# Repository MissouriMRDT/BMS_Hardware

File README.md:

Battery Management System- this year it DOES THINGS (for real though!).

New for 2022: <br/>
-Designed to monitor an 8s8p LiPo battery pack at a max 33.6V @ 160A peak. <br/>
-The Cell Monitoring circuit uses the AS358MTR-E1 Op-Amp as it could be powered off of pack voltage. <br/>
-Teensy 4.1 used as microcontroller for the board.

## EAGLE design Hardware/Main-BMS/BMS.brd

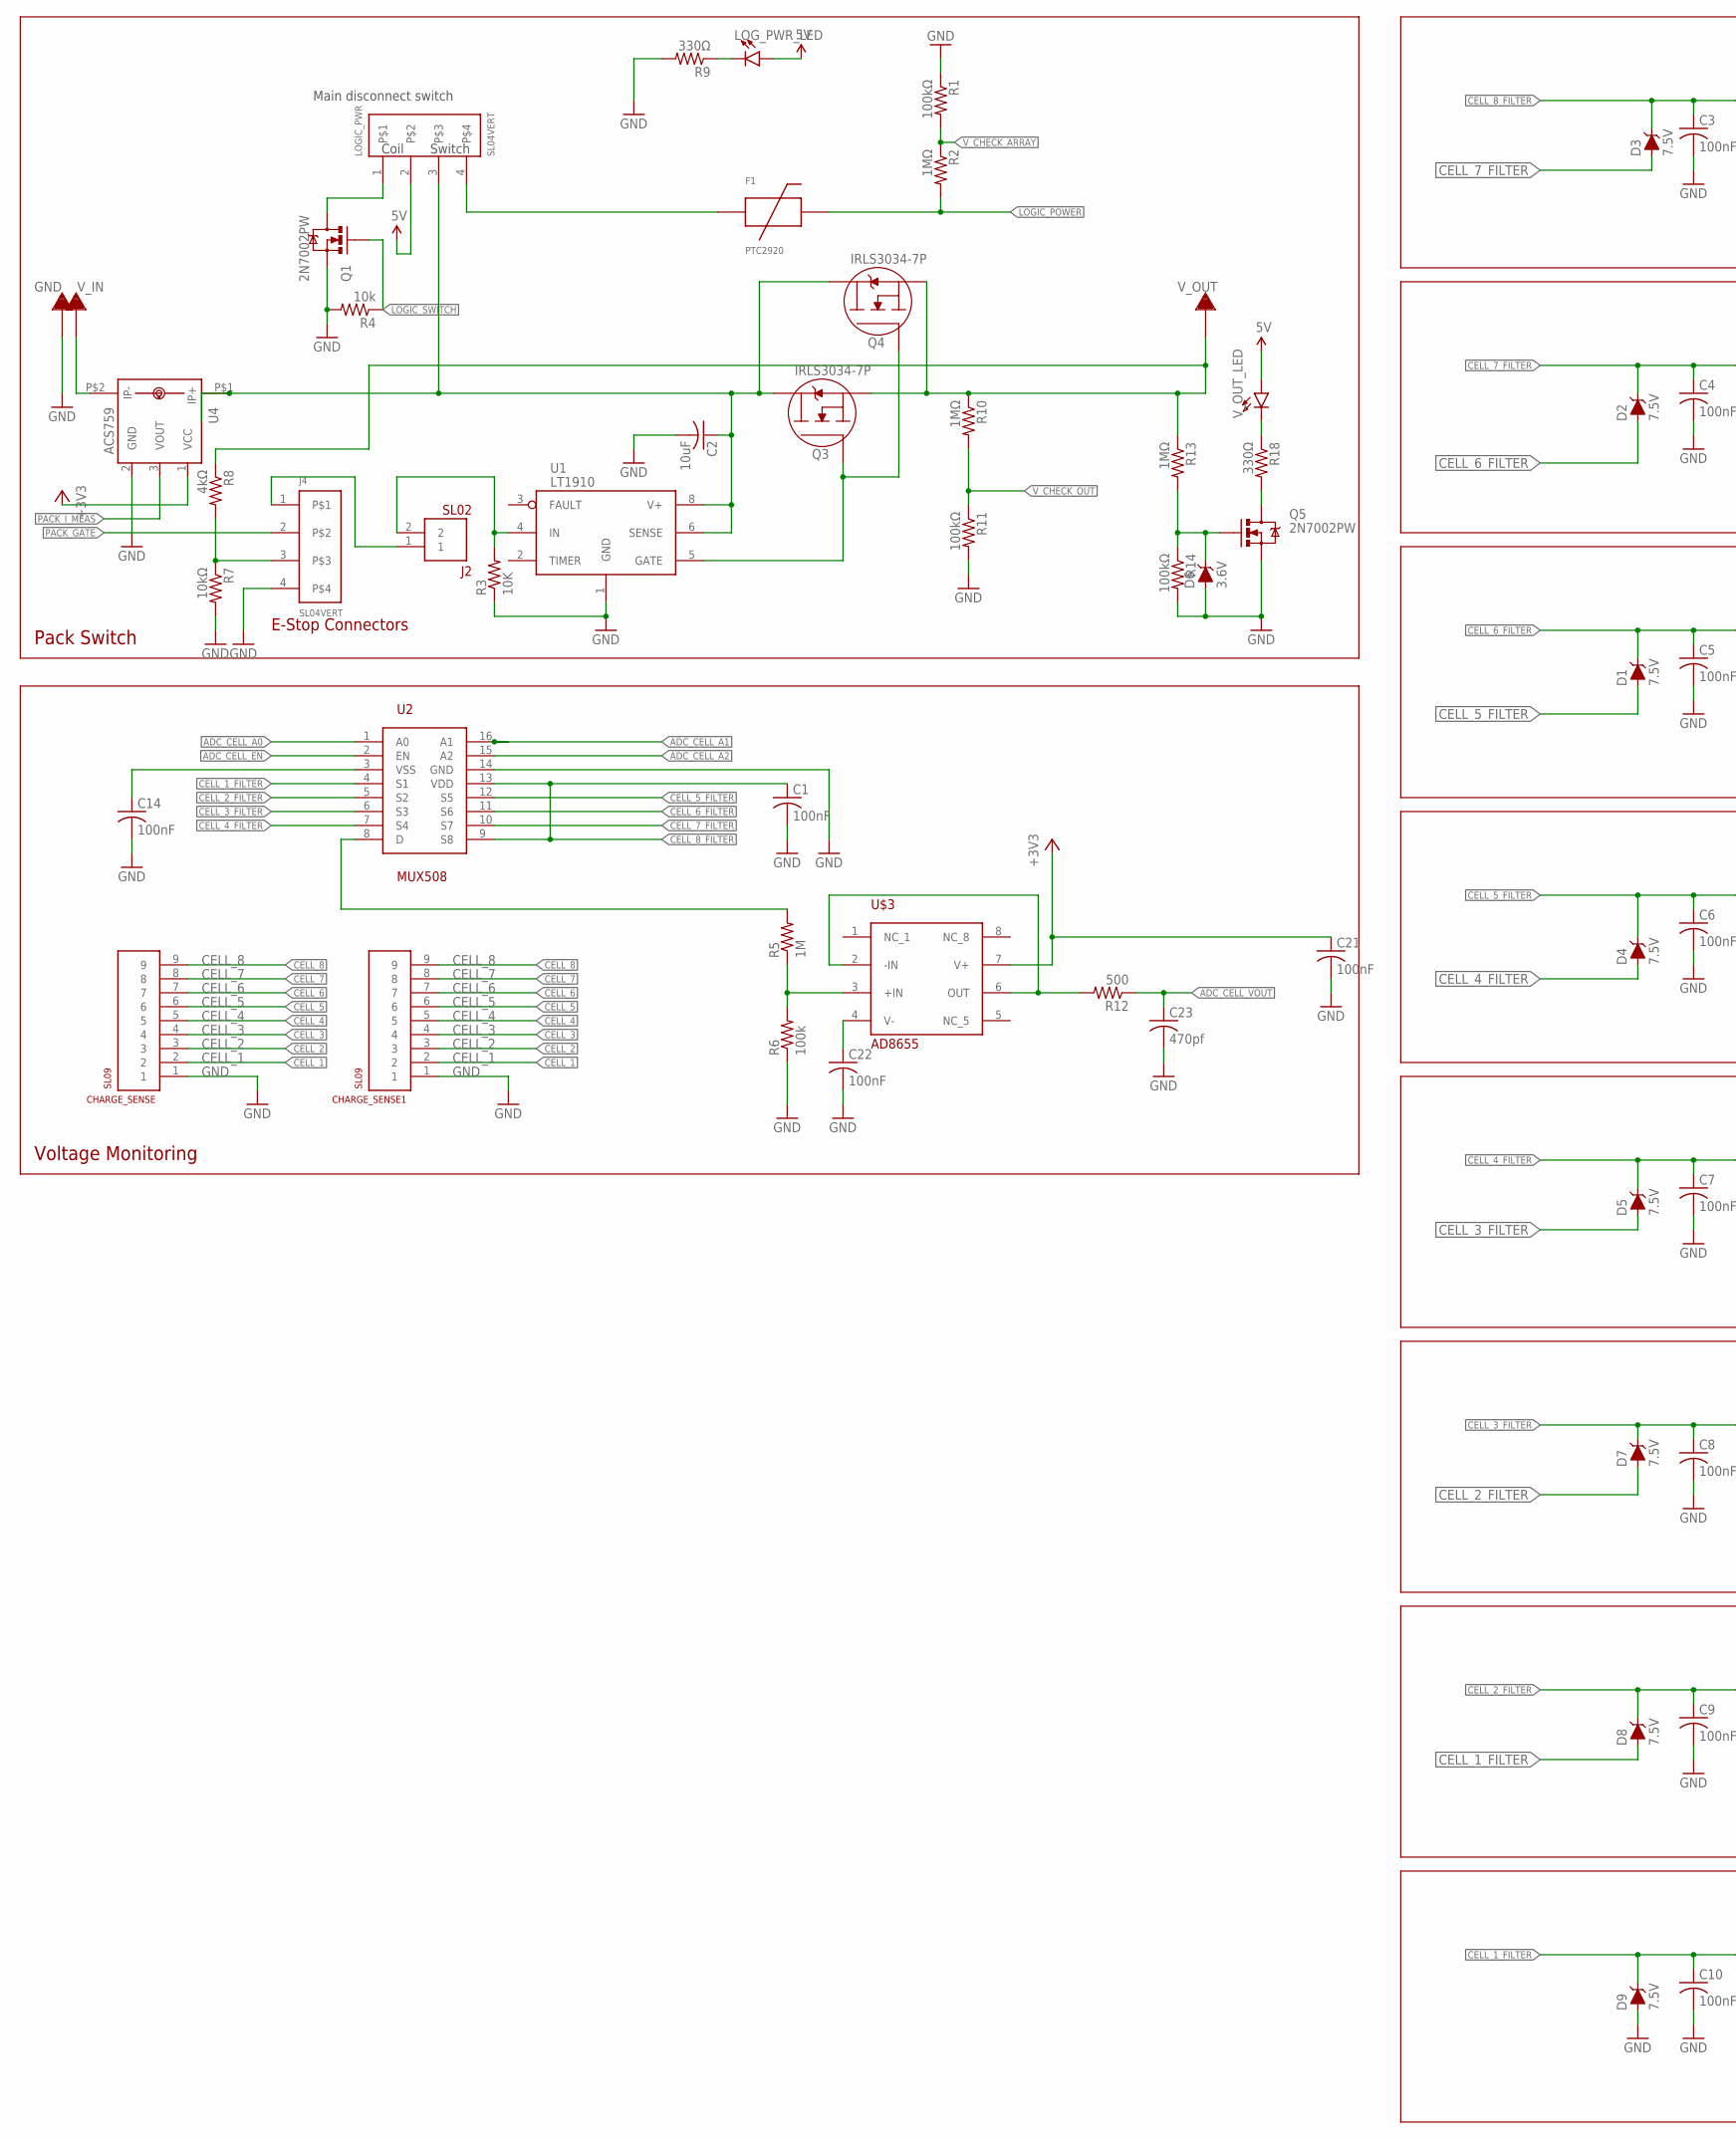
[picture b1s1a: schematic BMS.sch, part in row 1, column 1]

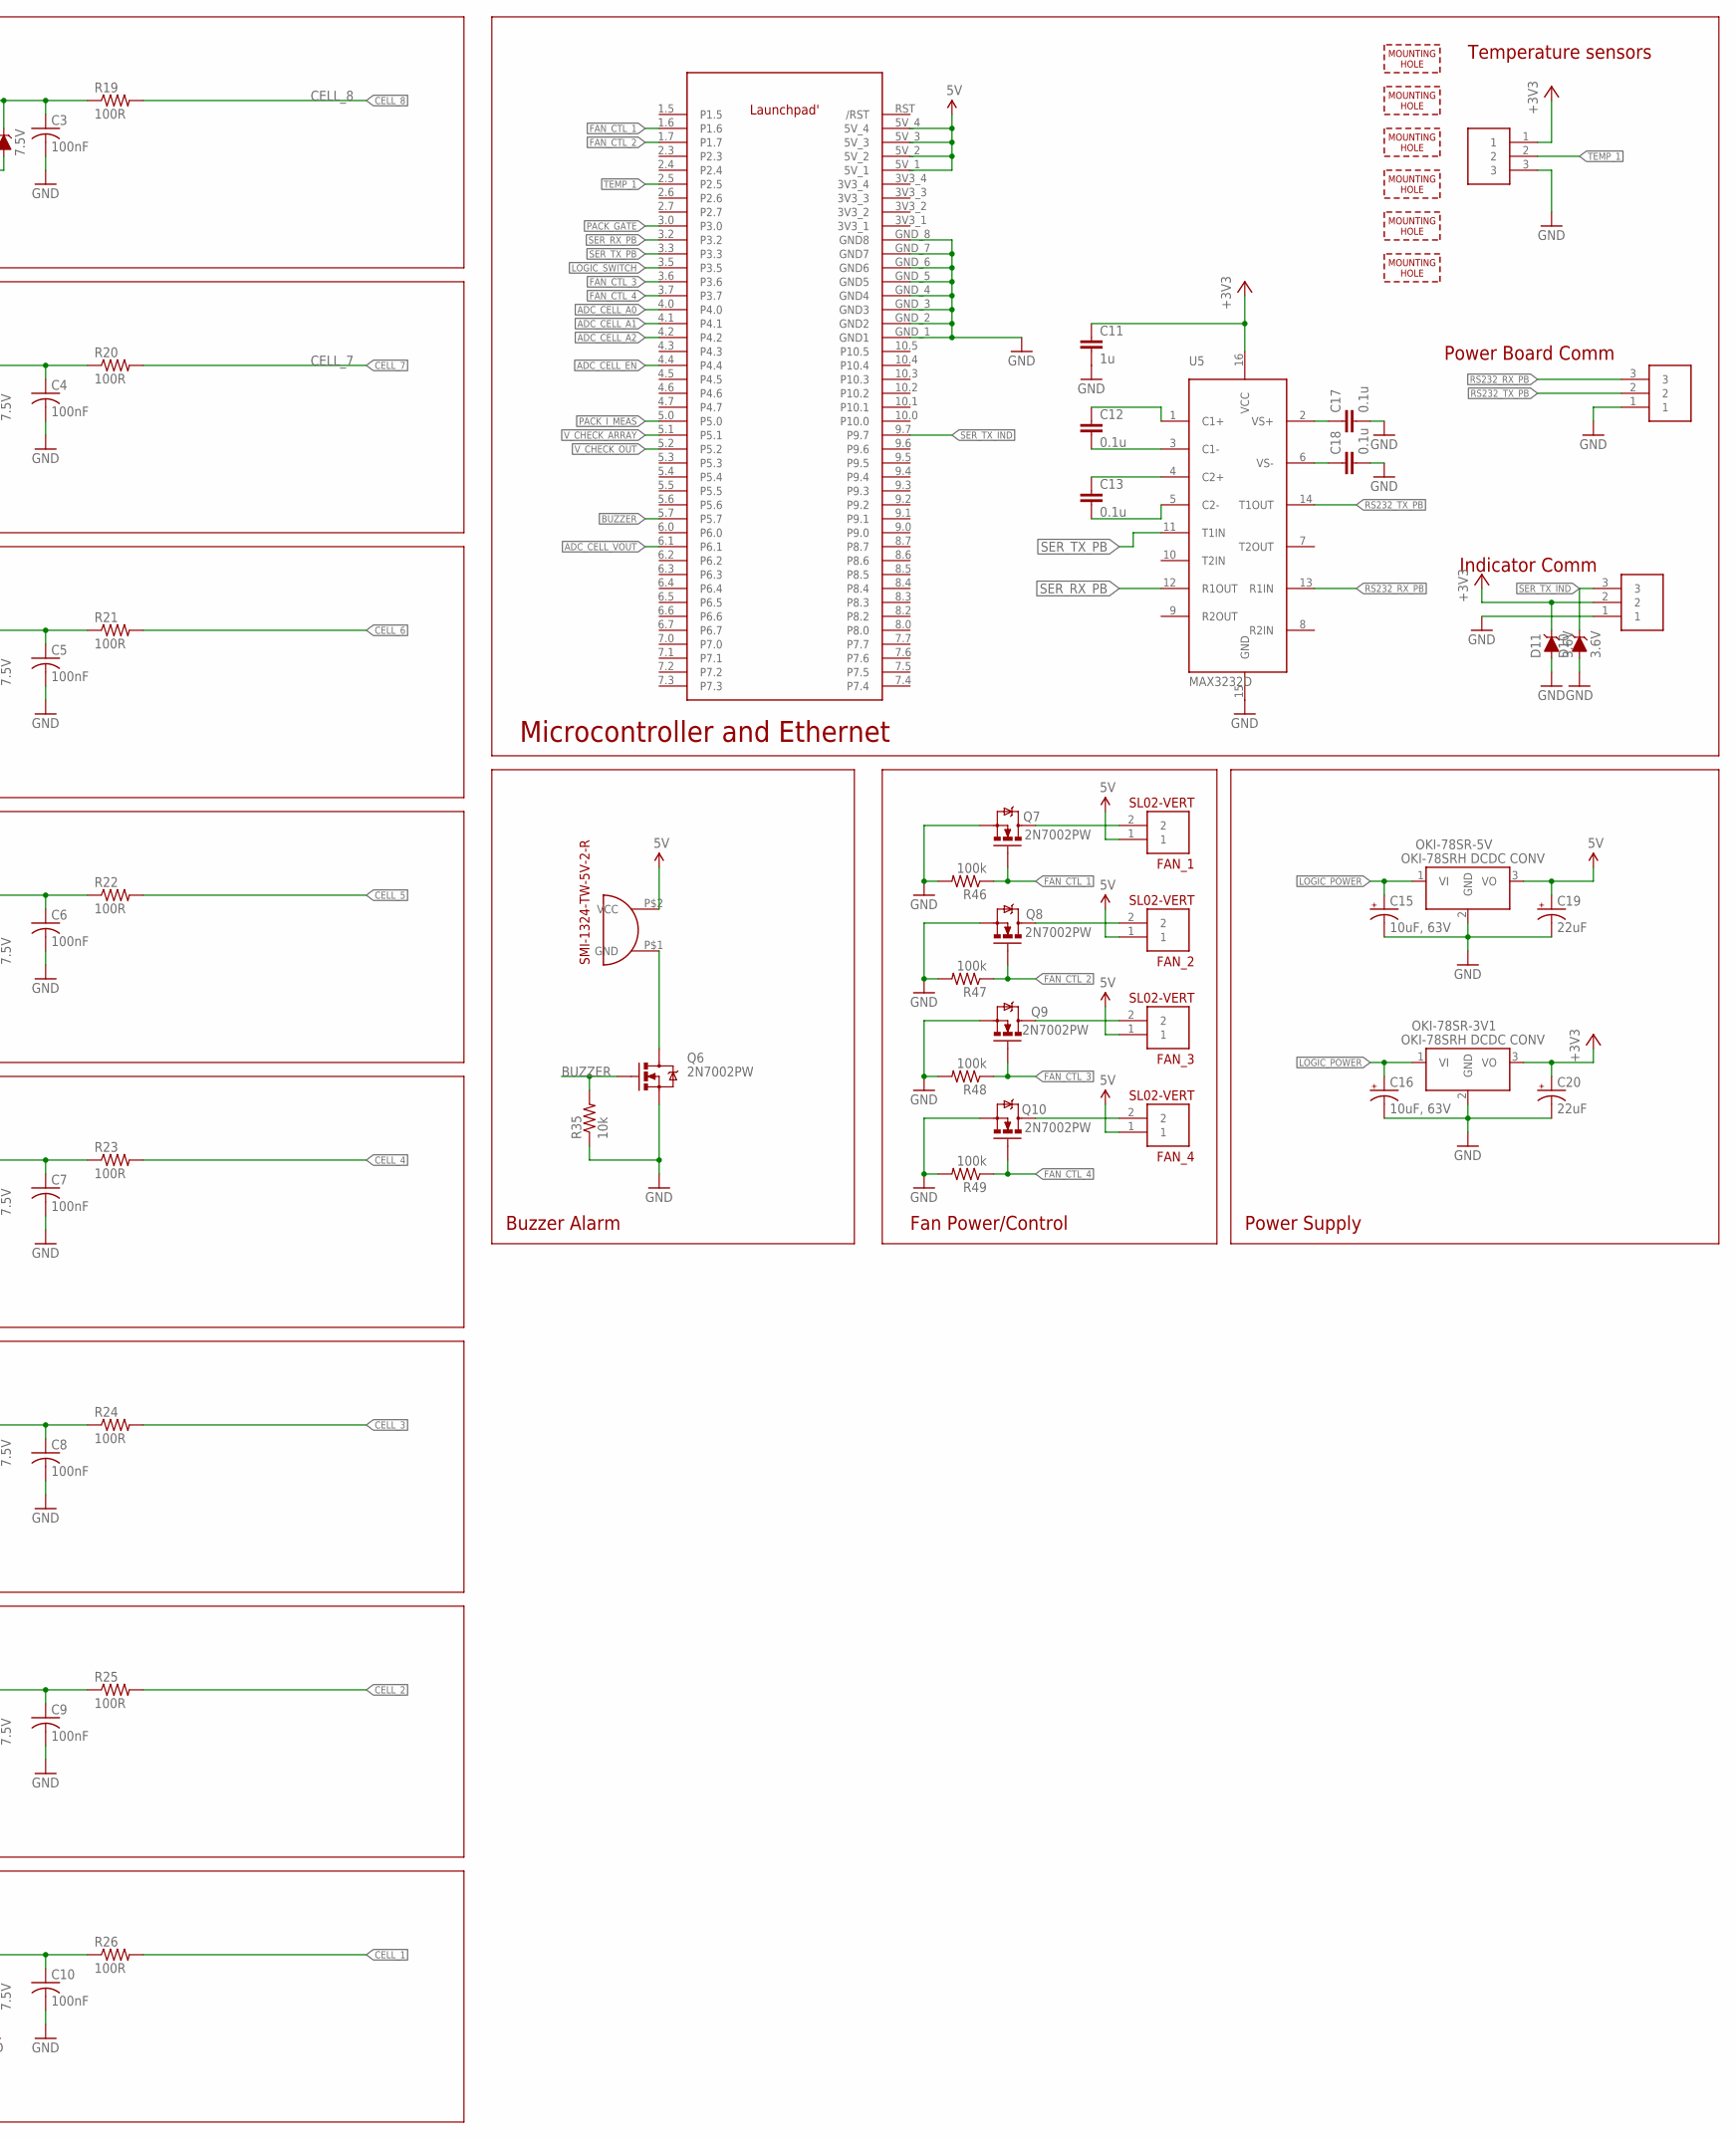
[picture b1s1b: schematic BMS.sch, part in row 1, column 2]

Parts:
C1, C3, C4, C5, C6, C7, C8, C9, C10, C14, C21, C22: 100nF; C0603
C2: 10uF; C0805
C11: 1u; 0805
C12, C13, C17, C18: 0.1u; 0805
C15, C16: 10uF, 63V; PANASONIC_D
C19, C20: 22uF; PANASONIC_D
C23: 470pf; C0603
CHARGE_SENSE, CHARGE_SENSE1: SL09; MOLEX-70543-0008
D1, D2, D3, D4, D5, D7, D8, D9: 7.5V; SOD-323
D6, D10, D11: 3.6V; SOD-323
F1: PTC2920; 2920
FAN_1, FAN_2, FAN_3, FAN_4: SL02-VERT; MOLEX-70543-0001
GND: TERMINAL_HOLE; LARGE_TERMINAL_HOLE
H1, H2, H3, H4, H5, H6: MOUNTING_HOLE#4; #4_SCREW
IC2: SMI-1324-TW-5V-2-R
J1: SL03; MOLEX-70543-0002
J2: SL02; MOLEX-70543-0001
J4: SL04VERT; MOLEX-70543-0003
LOGIC_PWR: SL04VERT; MOLEX-70543-0003
LOG_PWR_LED: LED1206; LED-1206
OKI-78SR-3V1: Q_OKI-78SR12; OKI-78SRH
OKI-78SR-5V: Q_OKI-78SR5; OKI-78SRH
Q1, Q5, Q6, Q7, Q8, Q9, Q10: 2N7002PW; SOT323
Q3, Q4: IRLS3034-7P; D2PAK-7
R1, R11, R14: 100kΩ; R0805
R2, R10, R13: 1MΩ; R0805
R3: 10K; 0603-RES
R4, R35: 10k; R0805
R5: 1M; M1206
R6: 100k; M1206
R7: 10kΩ; R0805
R8: 4kΩ; R0805
R9, R18: 330Ω; R0805
R12: 500; M1206
R19, R20, R21, R22, R23, R24, R25, R26: 100R; R0603
R46, R47, R48, R49: 100k; R0805
RS232_PB: SL03; MOLEX-70543-0002
TEMP_1: SL03; MOLEX-70543-0002
U1: LT1910; SO8
U2: MUX508; SOIC16
U3: MSP430R401R; MSP432R401R-LAUNCHPAD
U4: ACS759; ACS-PFF-LEADFORM
U5: MAX3232D; SOIC16
U$3: AD8655; SOIC8
V_IN: TERMINAL_HOLE; LARGE_TERMINAL_HOLE
V_OUT: TERMINAL_HOLE; LARGE_TERMINAL_HOLE
V_OUT_LED: LED1206; LED-1206

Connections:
5V: C19.+, FAN_1.1, FAN_2.1, FAN_3.1, FAN_4.1, IC2.P$2 (VCC), LOGIC_PWR.2, LOG_PWR_LED.A, OKI-78SR-5V.3 (VO), U3.5V_1, U3.5V_2, U3.5V_3, U3.5V_4, V_OUT_LED.A
+3V3: C11.1, C20.+, C21.1, D11.C, J1.2, OKI-78SR-3V1.3 (VO), TEMP_1.1, U4.1 (VCC), U5.16 (VCC), U$3.7 (V+)
ADC_CELL_A0: U2.1 (A0), U3.4.0
ADC_CELL_A1: U2.16 (A1), U3.4.1
ADC_CELL_A2: U2.15 (A2), U3.4.2
ADC_CELL_EN: U2.2 (EN), U3.4.4
ADC_CELL_VIN: R5.1, R6.2, U$3.3 (+IN)
ADC_CELL_VOUT: C23.1, R12.1, U3.6.1
BUZZER: Q6.1 (G), R35.2, U3.5.7
CELL_1: CHARGE_SENSE.2, CHARGE_SENSE1.2, R26.2
CELL_1_FILTER: C10.1, D8.A, D9.C, R26.1, U2.4 (S1)
CELL_2: CHARGE_SENSE.3, CHARGE_SENSE1.3, R25.2
CELL_2_FILTER: C9.1, D7.A, D8.C, R25.1, U2.5 (S2)
CELL_3: CHARGE_SENSE.4, CHARGE_SENSE1.4, R24.2
CELL_3_FILTER: C8.1, D5.A, D7.C, R24.1, U2.6 (S3)
CELL_4: CHARGE_SENSE.5, CHARGE_SENSE1.5, R23.2
CELL_4_FILTER: C7.1, D4.A, D5.C, R23.1, U2.7 (S4)
CELL_5: CHARGE_SENSE.6, CHARGE_SENSE1.6, R22.2
CELL_5_FILTER: C6.1, D1.A, D4.C, R22.1, U2.12 (S5)
CELL_6: CHARGE_SENSE.7, CHARGE_SENSE1.7, R21.2
CELL_6_FILTER: C5.1, D1.C, D2.A, R21.1, U2.11 (S6)
CELL_7: CHARGE_SENSE.8, CHARGE_SENSE1.8, R20.2
CELL_7_FILTER: C4.1, D2.C, D3.A, R20.1, U2.10 (S7)
CELL_8: CHARGE_SENSE.9, CHARGE_SENSE1.9, R19.2
CELL_8_FILTER: C1.1, C3.1, D3.C, R19.1, U2.9 (S8), U2.13 (VDD)
FAN_CTL_1: Q7.1 (G), R46.1, U3.1.6
FAN_CTL_2: Q8.1 (G), R47.1, U3.1.7
FAN_CTL_3: Q9.1 (G), R48.1, U3.3.6
FAN_CTL_4: Q10.1 (G), R49.1, U3.3.7
GND: C1.2, C2.2, C3.2, C4.2, C5.2, C6.2, C7.2, C8.2, C9.2, C10.2, C11.2, C14.2, C15.-, C16.-, C17.2, C18.2, C19.-, C20.-, C21.2, C22.2, C23.2, CHARGE_SENSE.1, CHARGE_SENSE1.1, D6.A, D9.A, D10.A, D11.A, GND.P$1, J1.1, J4.4, OKI-78SR-3V1.2 (GND), OKI-78SR-5V.2 (GND), Q1.2 (S), Q5.2 (S), Q6.2 (S), Q7.2 (S), Q8.2 (S), Q9.2 (S), Q10.2 (S), R1.1, R3.1, R4.2, R6.1, R7.2, R9.2, R11.2, R14.2, R35.1, R46.2, R47.2, R48.2, R49.2, RS232_PB.1, TEMP_1.3, U1.1 (GND), U2.14 (GND), U3.GND_1 (GND1), U3.GND_2 (GND2), U3.GND_3 (GND3), U3.GND_4 (GND4), U3.GND_5 (GND5), U3.GND_6 (GND6), U3.GND_7 (GND7), U3.GND_8 (GND8), U4.2 (GND), U5.15 (GND)
LOGIC_POWER: C15.+, C16.+, F1.P$2, OKI-78SR-3V1.1 (VI), OKI-78SR-5V.1 (VI), R2.2
LOGIC_SWITCH: Q1.1 (G), R4.1, U3.3.5
unnamed: J2.1, J4.1
unnamed: Q5.3 (D), R18.2
unnamed: C14.1, U2.3 (VSS)
unnamed: LOG_PWR_LED.C, R9.1
unnamed: J2.2, R3.2, U1.4 (IN)
unnamed: C22.1, U$3.4 (V-)
unnamed: LOGIC_PWR.1, Q1.3 (D)
unnamed: C13.1, U5.4 (C2+)
unnamed: R18.1, V_OUT_LED.C
unnamed: D6.C, Q5.1 (G), R13.2, R14.1
unnamed: J4.3, R7.1, R8.2
unnamed: C13.2, U5.5 (C2-)
unnamed: C17.1, U5.2 (VS+)
unnamed: F1.P$1, LOGIC_PWR.4
unnamed: R5.2, U2.8 (D)
unnamed: Q3.1 (GATE), Q4.1 (GATE), U1.5 (GATE)
unnamed: C12.1, U5.1 (C1+)
unnamed: C2.1, LOGIC_PWR.3, Q3.PAD (DRAIN), Q4.PAD (DRAIN), U1.6 (SENSE), U1.8 (V+), U4.P$1 (IP+)
unnamed: C12.2, U5.3 (C1-)
unnamed: C18.1, U5.6 (VS-)
unnamed: IC2.P$1 (GND), Q6.3 (D)
unnamed: FAN_1.2, Q7.3 (D)
unnamed: FAN_2.2, Q8.3 (D)
unnamed: FAN_3.2, Q9.3 (D)
unnamed: FAN_4.2, Q10.3 (D)
PACK_GATE: J4.2, U3.3.0
PACK_I_MEAS: U3.5.0, U4.3 (VOUT)
RC_FILTER: R12.2, U$3.2 (-IN), U$3.6 (OUT)
RS232_RX_PB: RS232_PB.3, U5.13 (R1IN)
RS232_TX_PB: RS232_PB.2, U5.14 (T1OUT)
SER_RX_PB: U3.3.2, U5.12 (R1OUT)
SER_TX_IND: D10.C, J1.3, U3.9.7
SER_TX_PB: U3.3.3, U5.11 (T1IN)
TEMP_1: TEMP_1.2, U3.2.5
V_CHECK_ARRAY: R1.2, R2.1, U3.5.1
V_CHECK_OUT: R10.2, R11.1, U3.5.2
V_IN: U4.P$2 (IP-), V_IN.P$1
V_OUT: Q3.2 (SOURCE), Q3.3 (SOURCE), Q3.4 (SOURCE), Q3.5 (SOURCE), Q3.6 (SOURCE), Q4.2 (SOURCE), Q4.3 (SOURCE), Q4.4 (SOURCE), Q4.5 (SOURCE), Q4.6 (SOURCE), R8.1, R10.1, R13.1, V_OUT.P$1

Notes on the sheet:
Pack Switch
Main disconnect switch
E-Stop Connectors
Power Supply
Buzzer Alarm
Fan Power/Control
Microcontroller and Ethernet
Voltage Monitoring
Temperature sensors
Switch
Coil
Indicator Comm
Power Board Comm

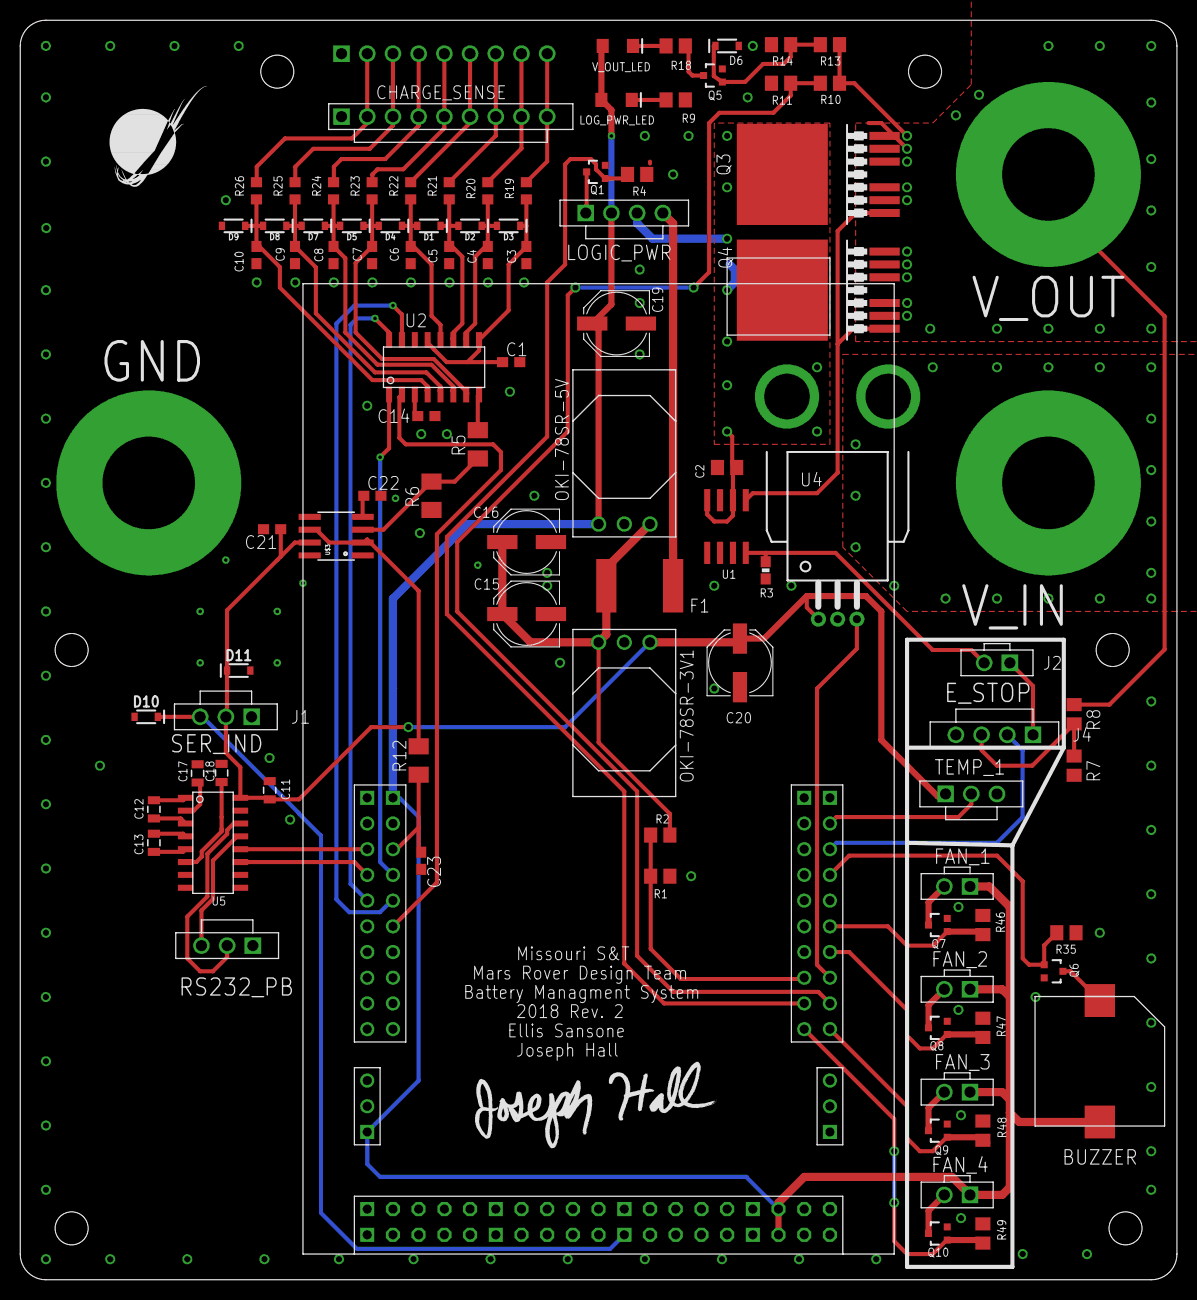
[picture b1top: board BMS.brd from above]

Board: 2 copper layers, 114.3 x 124.5 mm, 106 parts (1 on the bottom side), 70 nets.

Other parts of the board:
U$1: JOSEPH_HALL_SIGNATURE
U$9: MRDT_LOGO

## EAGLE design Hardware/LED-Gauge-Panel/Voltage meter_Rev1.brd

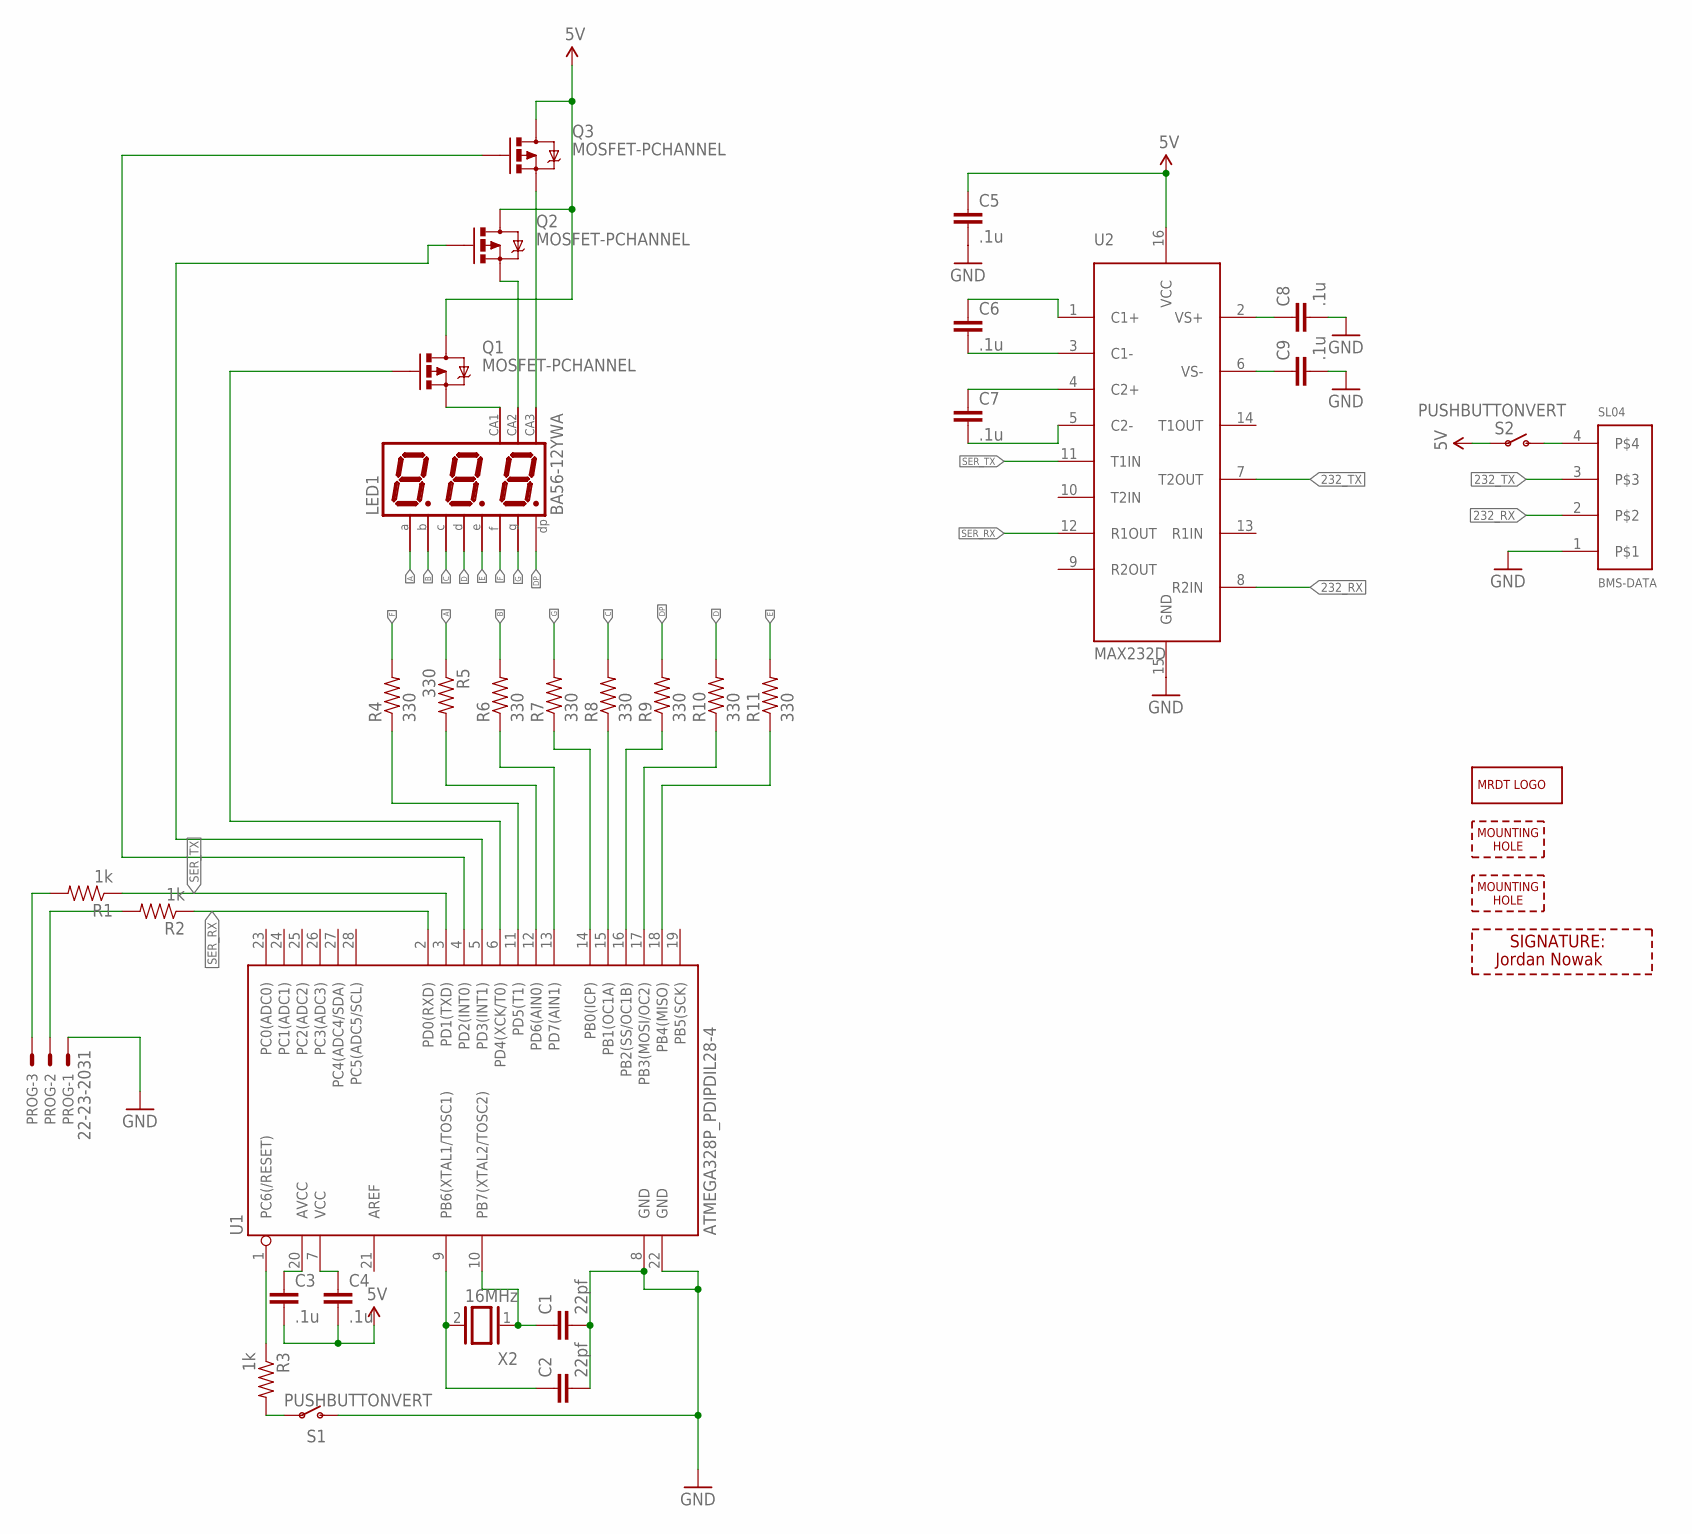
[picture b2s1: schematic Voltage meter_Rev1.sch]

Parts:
BMS-DATA: SL04; MOLEX_SL_04_TH
C1, C2: 22pf; 0805
C3, C4, C5, C6, C7, C8, C9: .1u; 0805
H1, H4: MOUNTING_HOLE#4; #4_SCREW
LED1: BA56-12YWA; BX56-12
LOGO1: MRDT_LOGO
PROG: 22-23-2031
Q1, Q2, Q3: MOSFET-PCHANNEL; SOT23-3
R1, R2, R3: 1k; 0805
R4, R5, R6, R7, R8, R9, R10, R11: 330; 0805
S1, S2: PUSHBUTTONVERT; APEM-MJTP1243
U1: ATMEGA328P_PDIPDIL28-4; CONN_IC_DIP_SOCKET_28POS
U2: MAX232D; SOIC16
U$1: JORDAN-NOWAK; JORDAN-NOWAK-SIG
X2: 16MHz; QS

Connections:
5V: C3.2, C4.2, C5.1, Q1.3 (D), Q2.3 (D), Q3.3 (D), S2.P$1, U2.16 (VCC)
232_RX: BMS-DATA.2, U2.8 (R2IN)
232_TX: BMS-DATA.3, U2.7 (T2OUT)
A: LED1.11 (A), R5.1
B: LED1.7 (B), R6.2
C: LED1.4 (C), R8.2
D: LED1.2 (D), R10.2
DP: LED1.3 (DP), R9.2
E: LED1.1 (E), R11.2
F: LED1.10 (F), R4.2
G: LED1.5 (G), R7.2
GND: BMS-DATA.1, C1.2, C2.2, C5.2, C8.2, C9.2, PROG.1, S1.P$2 (S), U1.8 (GND), U1.22 (GND), U2.15 (GND)
unnamed: R7.1, U1.14 (PB0(ICP))
unnamed: LED1.12 (CA), Q1.2 (S)
unnamed: LED1.9 (CA), Q2.2 (S)
unnamed: LED1.8 (CA), Q3.2 (S)
unnamed: R8.1, U1.15 (PB1(OC1A))
unnamed: R9.1, U1.16 (PB2(SS/OC1B))
unnamed: BMS-DATA.4, S2.P$2 (S)
unnamed: R5.2, U1.12 (PD6(AIN0))
unnamed: R10.1, U1.17 (PB3(MOSI/OC2))
unnamed: R11.1, U1.18 (PB4(MISO))
unnamed: C8.1, U2.2 (VS+)
unnamed: PROG.2, R2.2
unnamed: R3.2, S1.P$1
unnamed: PROG.3, R1.2
unnamed: C4.1, U1.7 (VCC)
unnamed: C3.1, U1.20 (AVCC)
unnamed: R6.1, U1.13 (PD7(AIN1))
unnamed: R4.1, U1.11 (PD5(T1))
unnamed: R3.1, U1.1 (PC6(/RESET))
unnamed: C6.1, U2.1 (C1+)
unnamed: C6.2, U2.3 (C1-)
unnamed: C7.1, U2.4 (C2+)
unnamed: C7.2, U2.5 (C2-)
unnamed: C9.1, U2.6 (VS-)
unnamed: C2.1, U1.9 (PB6(XTAL1/TOSC1)), X2.2
unnamed: C1.1, U1.10 (PB7(XTAL2/TOSC2)), X2.1
Q4: Q3.1 (G), U1.4 (PD2(INT0))
Q5: Q2.1 (G), U1.5 (PD3(INT1))
Q6: Q1.1 (G), U1.6 (PD4(XCK/T0))
SER_RX: R2.1, U1.2 (PD0(RXD)), U2.12 (R1OUT)
SER_TX: R1.1, U1.3 (PD1(TXD)), U2.11 (T1IN)

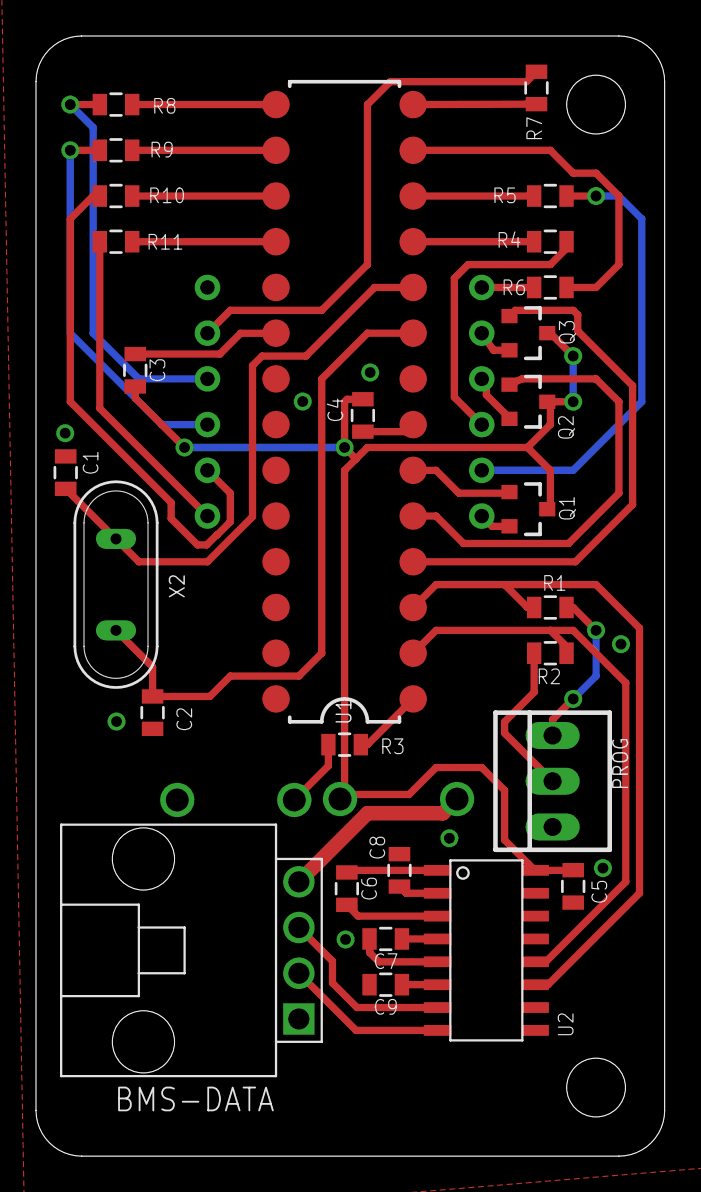
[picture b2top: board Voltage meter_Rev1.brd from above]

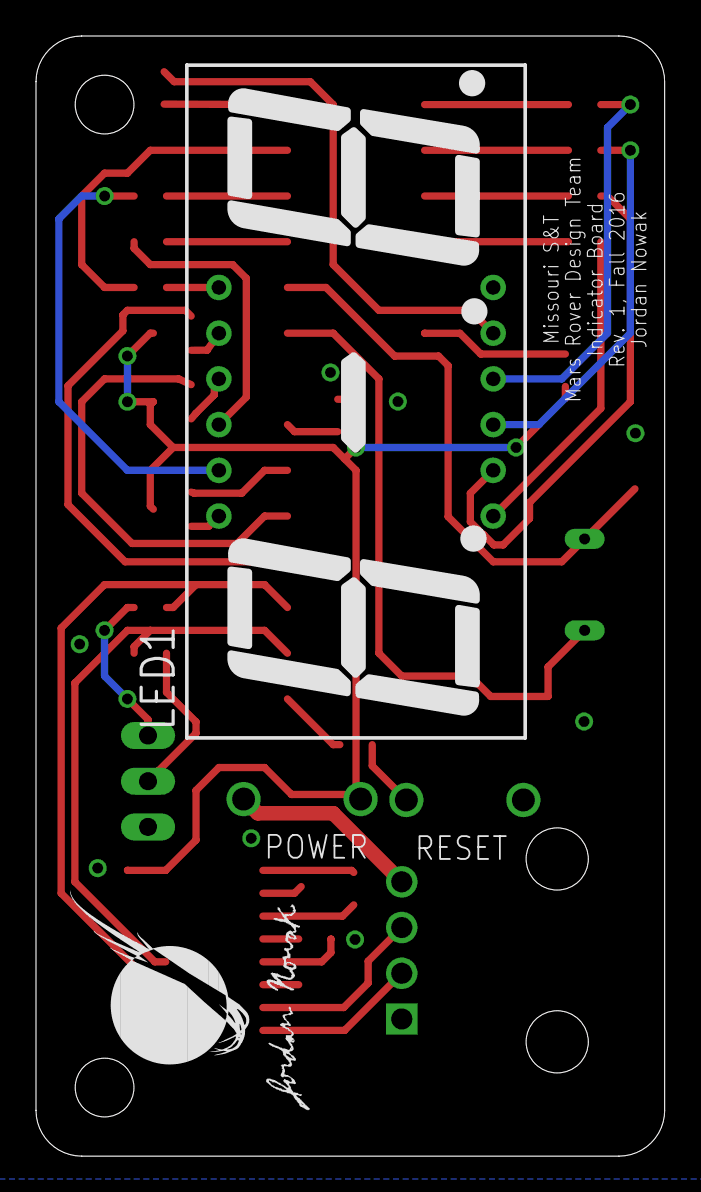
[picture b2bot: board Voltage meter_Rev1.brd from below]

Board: 2 copper layers, 34.9 x 62.2 mm, 35 parts (5 on the bottom side), 43 nets.

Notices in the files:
parts and their libraries:
SparkFun-Connectors: Licensing: Creative Commons ShareAlike 4.0 International - https://creativecommons.org/licenses/by-sa/4.0
SparkFun-Connectors: Licensing: CC v3.0 Share-Alike You are welcome to use this library for commercial purposes.
